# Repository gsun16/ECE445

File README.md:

# arduino-accordion

Inspired from the project https://hackaday.io/project/197399-arduino-esp32-standalone-accordion

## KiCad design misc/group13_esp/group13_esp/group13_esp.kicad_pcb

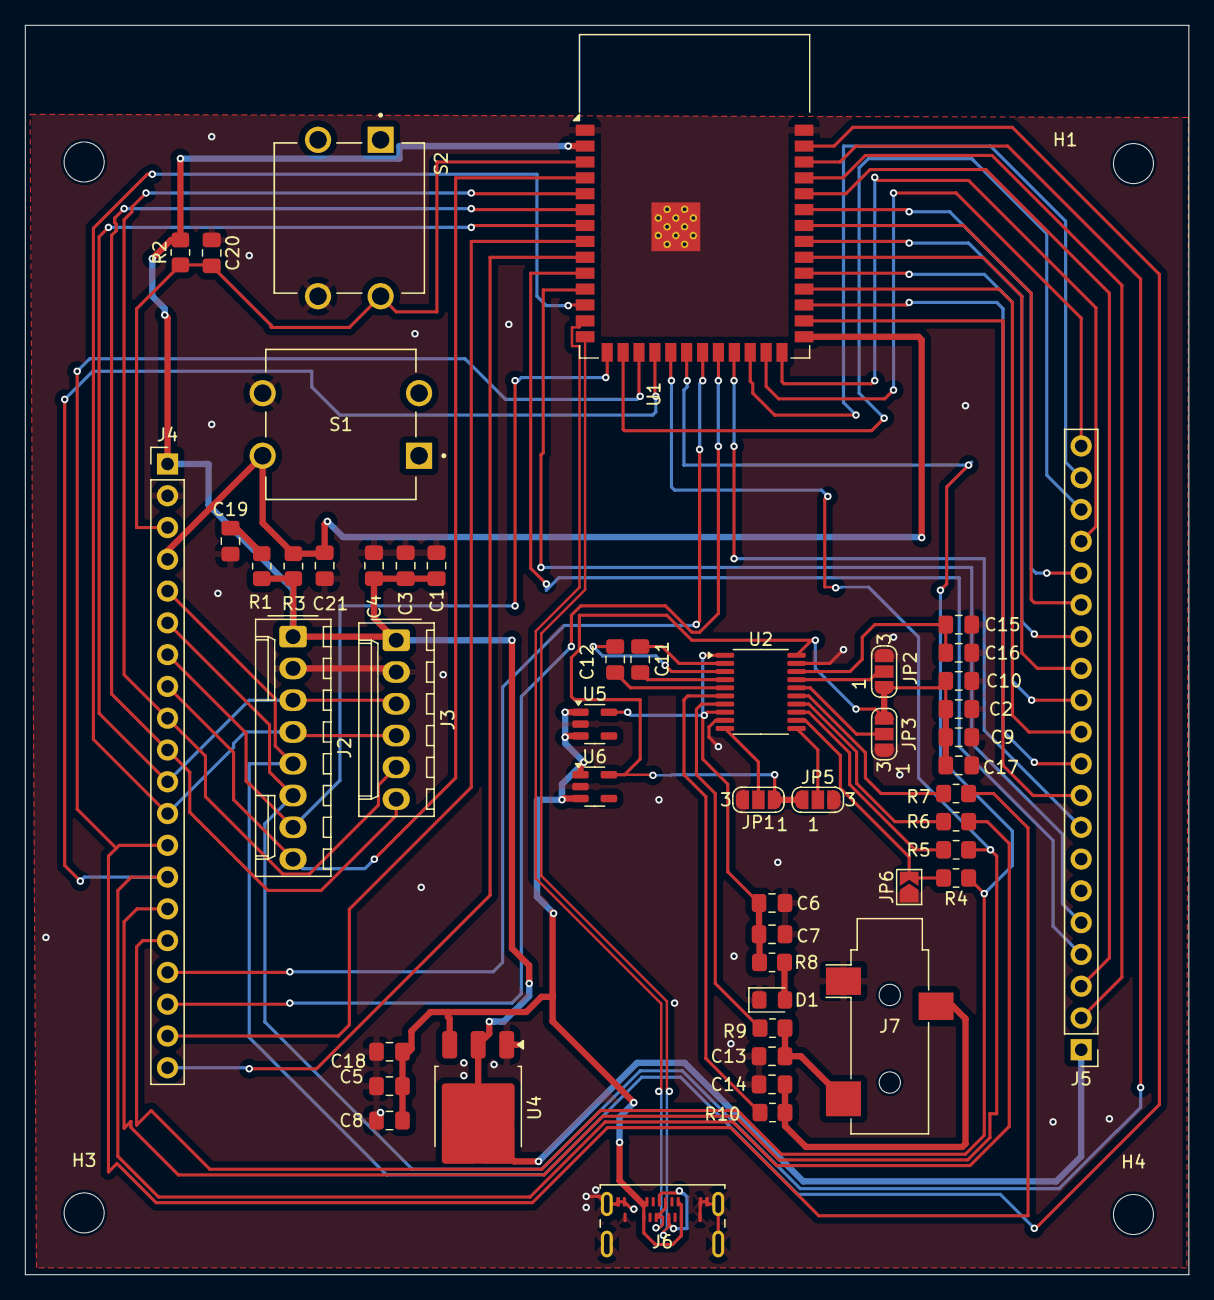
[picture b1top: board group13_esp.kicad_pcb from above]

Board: 2 copper layers, 93.0 x 99.9 mm, 54 parts (0 on the bottom side), 61 nets.

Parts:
C1, C2, C7, C9, C15, C18: 10uF; C_0805_2012Metric_Pad1.18x1.45mm_HandSolder
C3, C5, C6, C8, C10, C16, C17: 0.1uF; C_0805_2012Metric_Pad1.18x1.45mm_HandSolder
C4: 22uF; C_0805_2012Metric_Pad1.18x1.45mm_HandSolder
C11, C12, C13, C14: 2.2uF; C_0805_2012Metric_Pad1.18x1.45mm_HandSolder
C19, C20, C21: 1uF; C_0805_2012Metric_Pad1.18x1.45mm_HandSolder
D1: LED; LED_0805_2012Metric_Pad1.15x1.40mm_HandSolder
H1, H2, H3, H4: MountingHole; MountingHole_3.2mm_M3
J2: Conn_01x08; Molex_KK-254_AE-6410-08A_1x08_P2.54mm_Vertical
J3: Conn_01x06; Molex_KK-254_AE-6410-06A_1x06_P2.54mm_Vertical
J4, J5: Conn_01x20; PinHeader_1x20_P2.54mm_Vertical
J6: USB_C_Receptacle_USB2.0_16P; USB_C_Receptacle_Amphenol_124019772112A
J7: AudioJack3; Jack_3.5mm_CUI_SJ-3523-SMT_Horizontal
JP1: JUMPER_DEMP_GND; SolderJumper-3_P1.3mm_Open_RoundedPad1.0x1.5mm_NumberLabels
JP2: JUMPER_XSMT_3V3; SolderJumper-3_P1.3mm_Open_RoundedPad1.0x1.5mm_NumberLabels
JP3: JUMPER_FMT_GND; SolderJumper-3_P1.3mm_Open_RoundedPad1.0x1.5mm_NumberLabels
JP5: JUMPER_FLT_GND; SolderJumper-3_P1.3mm_Open_RoundedPad1.0x1.5mm_NumberLabels
JP6: JUMPER_SCK_GND; SolderJumper-2_P1.3mm_Open_TrianglePad1.0x1.5mm
R1: 10k; R_0805_2012Metric_Pad1.20x1.40mm_HandSolder
R2, R3: 100k; R_0805_2012Metric_Pad1.20x1.40mm_HandSolder
R4, R5, R6, R7: 22; R_0805_2012Metric_Pad1.20x1.40mm_HandSolder
R8: 1k; R_0805_2012Metric_Pad1.20x1.40mm_HandSolder
R9, R10: 470; R_0805_2012Metric_Pad1.20x1.40mm_HandSolder
S1, S2: TL1100F160Q; SW_TL1100F160Q
U1: ESP32-S3-WROOM-1
U2: PCM5102; TSSOP-20_4.4x6.5mm_P0.65mm
U4: AZ1117-3.3; TO-252-3_TabPin2
U5, U6: ME6211C33M5; SOT-23-5

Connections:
+3.3V: C1.2, C3.2, C4.2, J2.1, J3.1, J4.1, J5.1, R1.2, R2.2, R3.2, U1.2 (3V3), U4.2 (VO)
+5V: C5.1, C8.1, C18.2, J6.A4 (VBUS), J6.A9 (VBUS), J6.B4 (VBUS), J6.B9 (VBUS), U4.3 (VI), U5.1 (V_{IN}), U5.3 (CE), U6.1 (V_{IN}), U6.3 (CE)
/AVDD: C6.1, C7.1, R8.1, U2.1 (CPVDD), U2.8 (AVDD), U5.5 (V_{OUT})
/BCK: J4.15, R5.1, U1.19 (IO11)
/CLK: J2.4, J3.4, J4.12, U1.12 (IO8)
/D+: J6.A6 (D+), J6.B6 (D+), U1.14 (USB_D+)
/D-: J6.A7 (D-), J6.B7 (D-), U1.13 (USB_D-)
/DEMP: JP1.2 (C), U2.10 (DEMP)
/DIN: J4.14, R6.1, U1.18 (IO10)
/DVDD: C2.2, C9.1, C10.1, C17.2, JP1.1 (A), JP2.1 (A), JP3.1 (A), JP5.1 (A), U2.20 (DVDD), U6.5 (V_{OUT})
/EN: C20.2, J4.3, R2.1, S2.2, U1.3 (EN)
/FLT: JP5.2 (C), U2.11 (FLT)
/FMT: JP3.2 (C), U2.16 (FMT)
/LRCK: J4.13, R7.1, U1.17 (IO9)
/Q1: J2.5, J4.5, U1.39 (IO1)
/Q2: J2.6, J4.6, U1.38 (IO2)
/Q3: J2.7, J4.7, U1.15 (IO3)
/Q4: J2.8, J4.8, U1.4 (IO4)
/Q5: J3.5, J4.9, U1.5 (IO5)
/Q6: J3.6, J4.10, U1.6 (IO6)
/SCK: J4.16, R4.1, U1.20 (IO12)
/SH/LD: J2.3, J3.3, J4.11, U1.7 (IO7)
/Strapping: C21.2, J4.4, R3.1, S1.2, U1.27 (IO0)
/XSMT: JP2.2 (C), U2.17 (XSMT)
GND: C1.1, C2.1, C3.1, C4.1, C5.2, C6.2, C7.2, C8.2, C9.2, C10.2, C13.2, C14.1, C15.2, C16.2, C17.1, C18.1, C19.1, C20.1, C21.1, D1.1 (K), J2.2, J3.2, J4.2, J6.A1 (GND), J6.A12 (GND), J6.B1 (GND), J6.B12 (GND), J6.S1 (SHIELD), J7.S, JP1.3 (B), JP2.3 (B), JP3.3 (B), JP5.3 (B), JP6.1 (A), S1.4, S2.4, U1.1 (GND), U1.40 (GND), U1.41 (GND), U2.9 (AGND), U2.19 (DGND), U4.1 (GND), U5.2 (V_{SS}), U6.2 (V_{SS})
unnamed: C13.1, J7.T, R9.2
unnamed: C14.2, J7.R, R10.1
unnamed: C19.2, R1.1
unnamed: D1.2 (A), R8.2
unnamed: J4.17, U1.21 (IO13)
unnamed: J4.18, U1.22 (IO14)
unnamed: J4.19, U1.8 (IO15)
unnamed: J4.20, U1.9 (IO16)
unnamed: J5.2, U1.37 (TXD0)
unnamed: J5.3, U1.36 (RXD0)
unnamed: J5.4, U1.10 (IO17)
unnamed: J5.5, U1.11 (IO18)
unnamed: J5.8, U1.23 (IO21)
unnamed: J5.9, U1.28 (IO35)
unnamed: J5.10, U1.29 (IO36)
unnamed: J5.11, U1.30 (IO37)
unnamed: J5.12, U1.31 (IO38)
unnamed: J5.13, U1.32 (IO39)
unnamed: J5.14, U1.33 (IO40)
unnamed: J5.15, U1.34 (IO41)
unnamed: J5.16, U1.35 (IO42)
unnamed: J5.17, U1.26 (IO45)
unnamed: J5.18, U1.16 (IO46)
unnamed: J5.19, U1.24 (IO47)
unnamed: J5.20, U1.25 (IO48)
unnamed: JP6.2 (B), R4.2, U2.12 (SCK)
unnamed: R5.2, U2.13 (BCK)
unnamed: C11.2, U2.4 (CAPM)
unnamed: C11.1, U2.2 (CAPP)
unnamed: C12.1, U2.3 (CPGND)
unnamed: R6.2, U2.14 (DIN)
unnamed: C15.1, C16.1, U2.18 (LDOO)
unnamed: R7.2, U2.15 (LRCK)
unnamed: R10.2, U2.6 (OUTL)
unnamed: R9.1, U2.7 (OUTR)
unnamed: C12.2, U2.5 (VNEG)

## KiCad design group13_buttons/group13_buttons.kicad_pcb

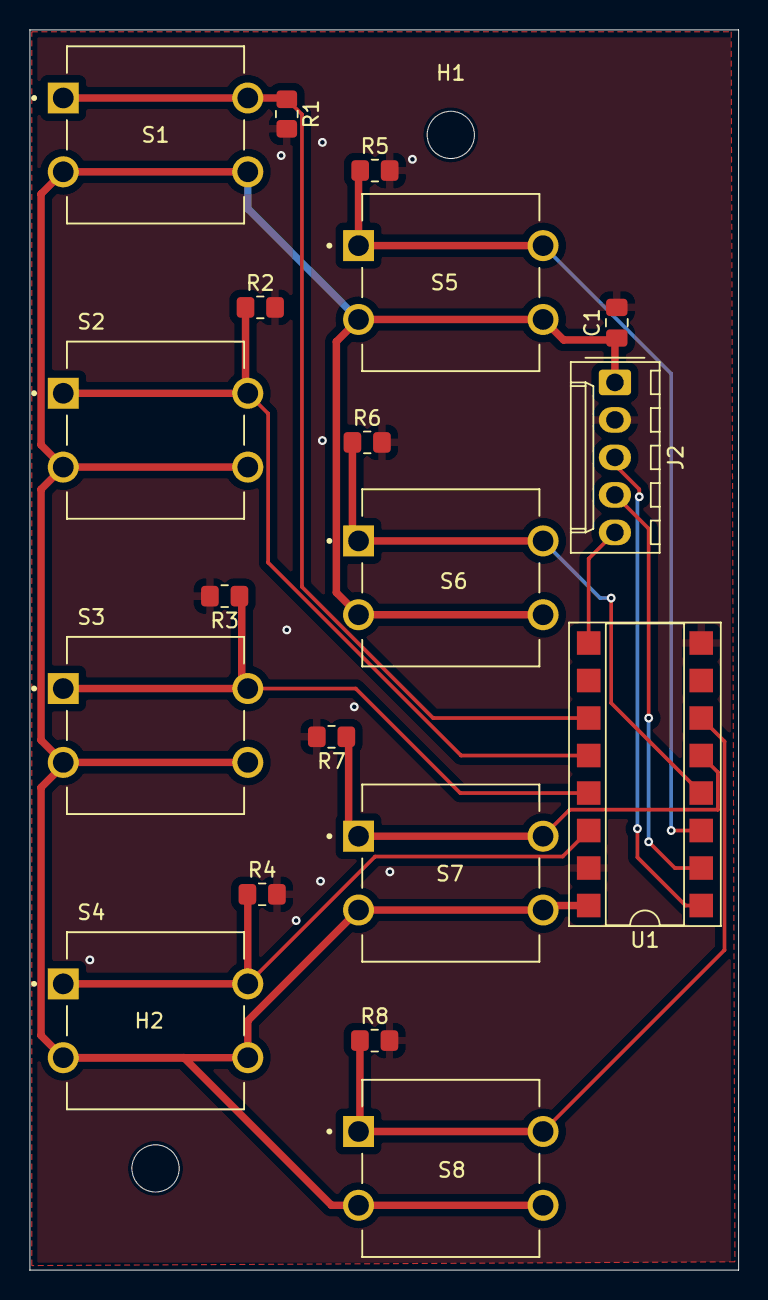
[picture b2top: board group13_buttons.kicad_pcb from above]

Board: 2 copper layers, 48.0 x 84.0 mm, 21 parts (0 on the bottom side), 13 nets.

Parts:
C1: 1uF; C_0805_2012Metric_Pad1.18x1.45mm_HandSolder
H1, H2: MountingHole; MountingHole_3.2mm_M3
J2: Conn_01x05; Molex_KK-254_AE-6410-05A_1x05_P2.54mm_Vertical
R1, R2, R3, R4, R5, R6, R7, R8: 10k; R_0805_2012Metric_Pad1.20x1.40mm_HandSolder
S1, S2, S3, S4, S5, S6, S7, S8: TL1100F160Q; SW_TL1100F160Q
U1: 74HC165; DIP-16_W7.62mm_SMDSocket_SmallPads

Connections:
+3.3V: C1.1, J2.1, S1.3, S1.4, S2.3, S2.4, S3.3, S3.4, S4.3, S4.4, S5.3, S5.4, S6.3, S6.4, S7.3, S7.4, S8.3, S8.4, U1.16 (VCC)
/CLK: J2.4, U1.2 (CP)
/D0: R1.1, S1.1, S1.2, U1.11 (D0)
/D1: R2.1, S2.1, S2.2, U1.12 (D1)
/D2: R3.1, S3.1, S3.2, U1.13 (D2)
/D3: R4.1, S4.1, S4.2, U1.14 (D3)
/D4: R5.1, S5.1, S5.2, U1.3 (D4)
/D5: R6.1, S6.1, S6.2, U1.4 (D5)
/D6: R7.1, S7.1, S7.2, U1.5 (D6)
/D7: R8.1, S8.1, S8.2, U1.6 (D7)
/PL: J2.3, U1.1 (~PL)
/Q1: J2.5, U1.9 (Q7)
GND: C1.2, J2.2, R1.2, R2.2, R3.2, R4.2, R5.2, R6.2, R7.2, R8.2, U1.8 (GND), U1.15 (~CE)

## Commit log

2023-09-29 Initial version.
2024-08-19 Refactoring code to use OOP and emulate Output to the console.
2024-08-19 Using map and vector to make my life easier.
2024-08-21 Refactoring the Note and Chord classes to have pre defined Notes and Chords.
2024-08-29 Using Phil Schatzmann's synth/audio tools.
2024-08-29 Removing .pio from git repo.
2024-08-29 Formatting the IF properly.
2024-08-31 Processing 512kb of data every cycle.
2024-09-05 Using AMY, simply amazing
2024-09-05 Making the voicer leaner
2024-09-07 Adding a new type of keyboard.
2024-09-07 Using sprintf to set the voice being played.
2025-03-06 16 keys working
2025-04-01 add pcbs
2025-04-01 midi to chord events?
2025-04-01 midi to chords done
2025-04-24 esp s3
2025-04-25 working on 6 keyboards
2025-04-25 2 keyboards working
2025-04-25 6 keyboards works well, remapping
2025-04-27 chords working, reduce button read time
2025-04-28 increase sample rate
2025-05-08 reformat
2025-05-08 upload gsun lab nb
2025-05-08 upload notes and figs
